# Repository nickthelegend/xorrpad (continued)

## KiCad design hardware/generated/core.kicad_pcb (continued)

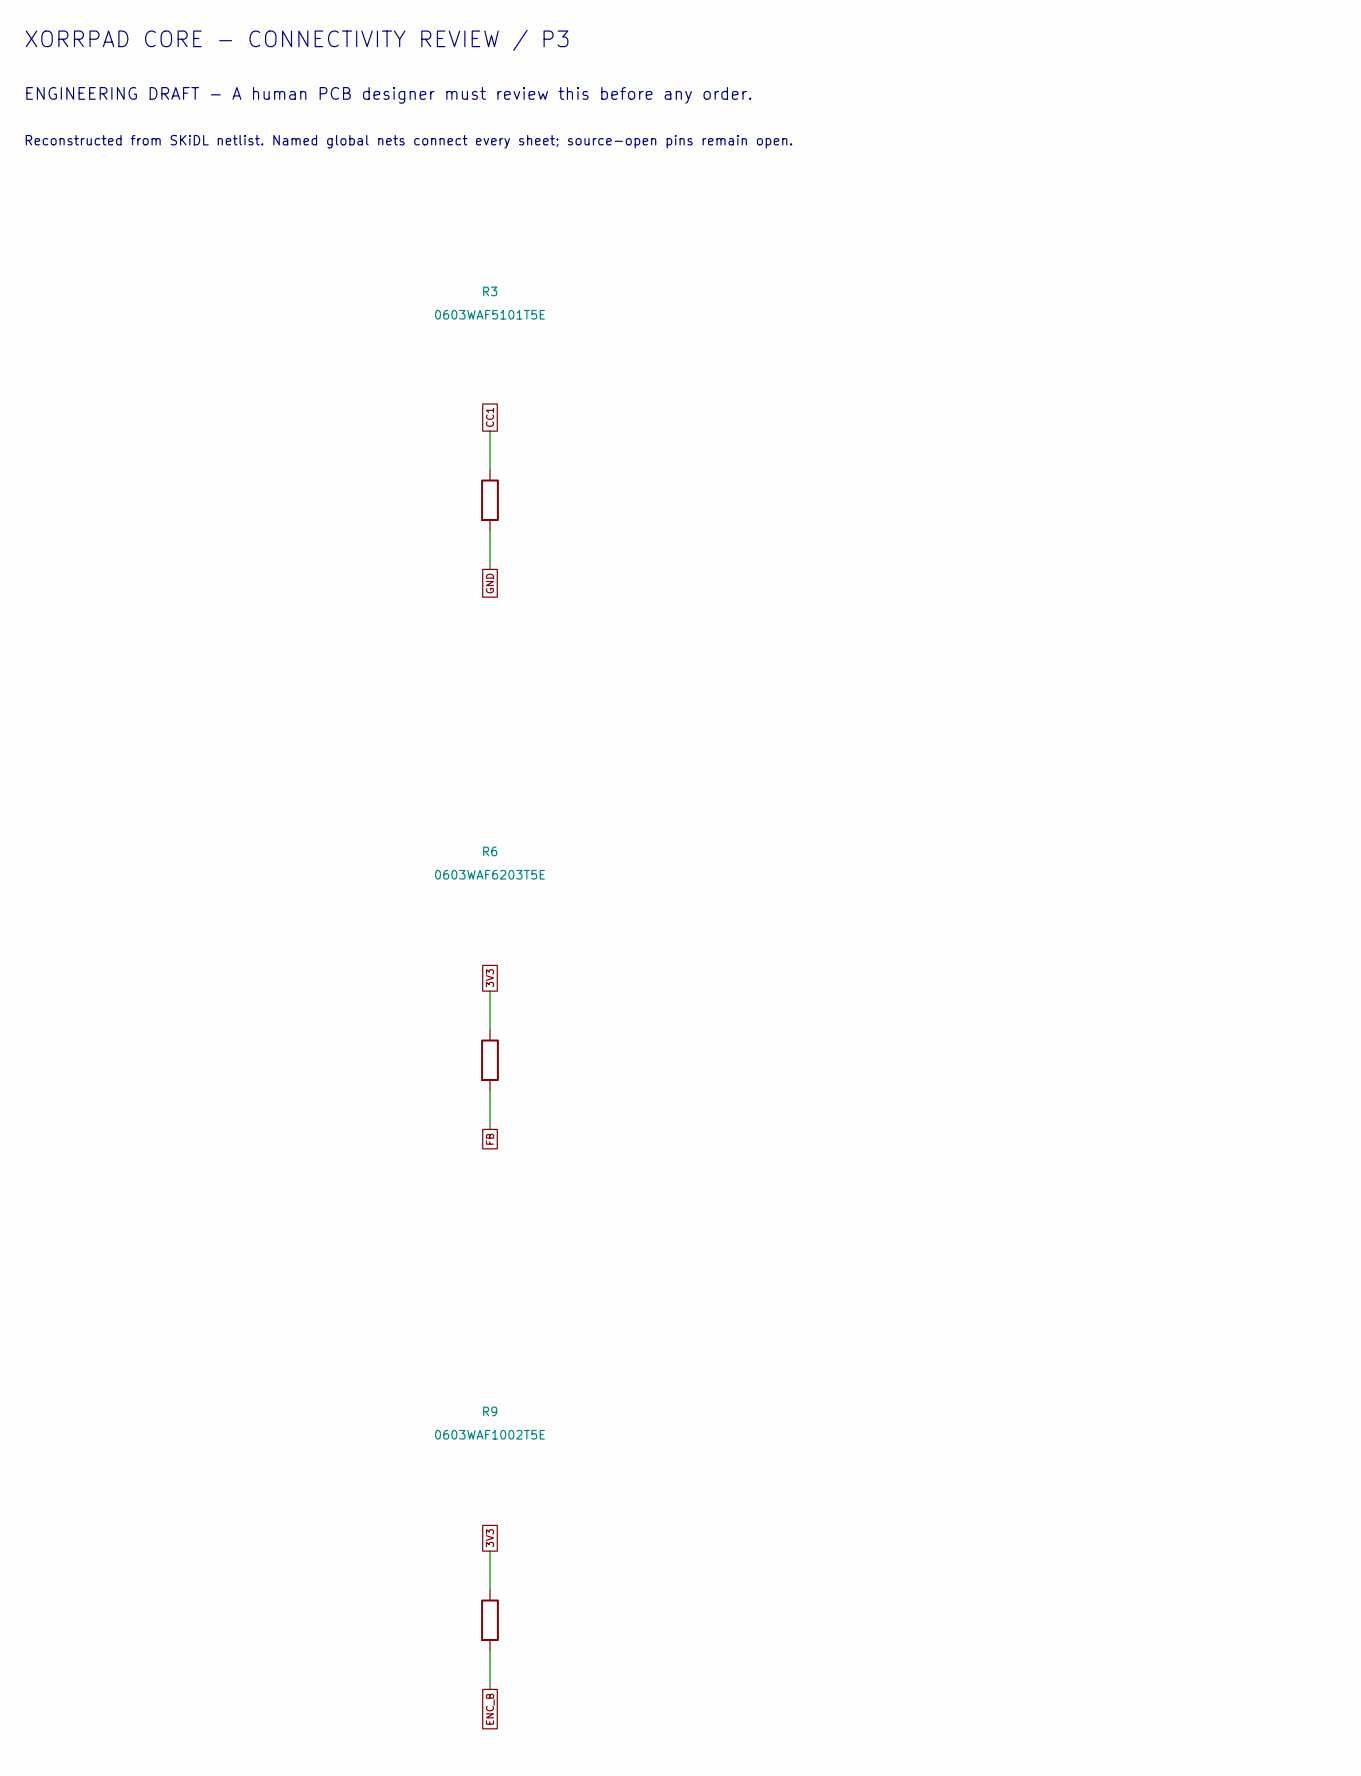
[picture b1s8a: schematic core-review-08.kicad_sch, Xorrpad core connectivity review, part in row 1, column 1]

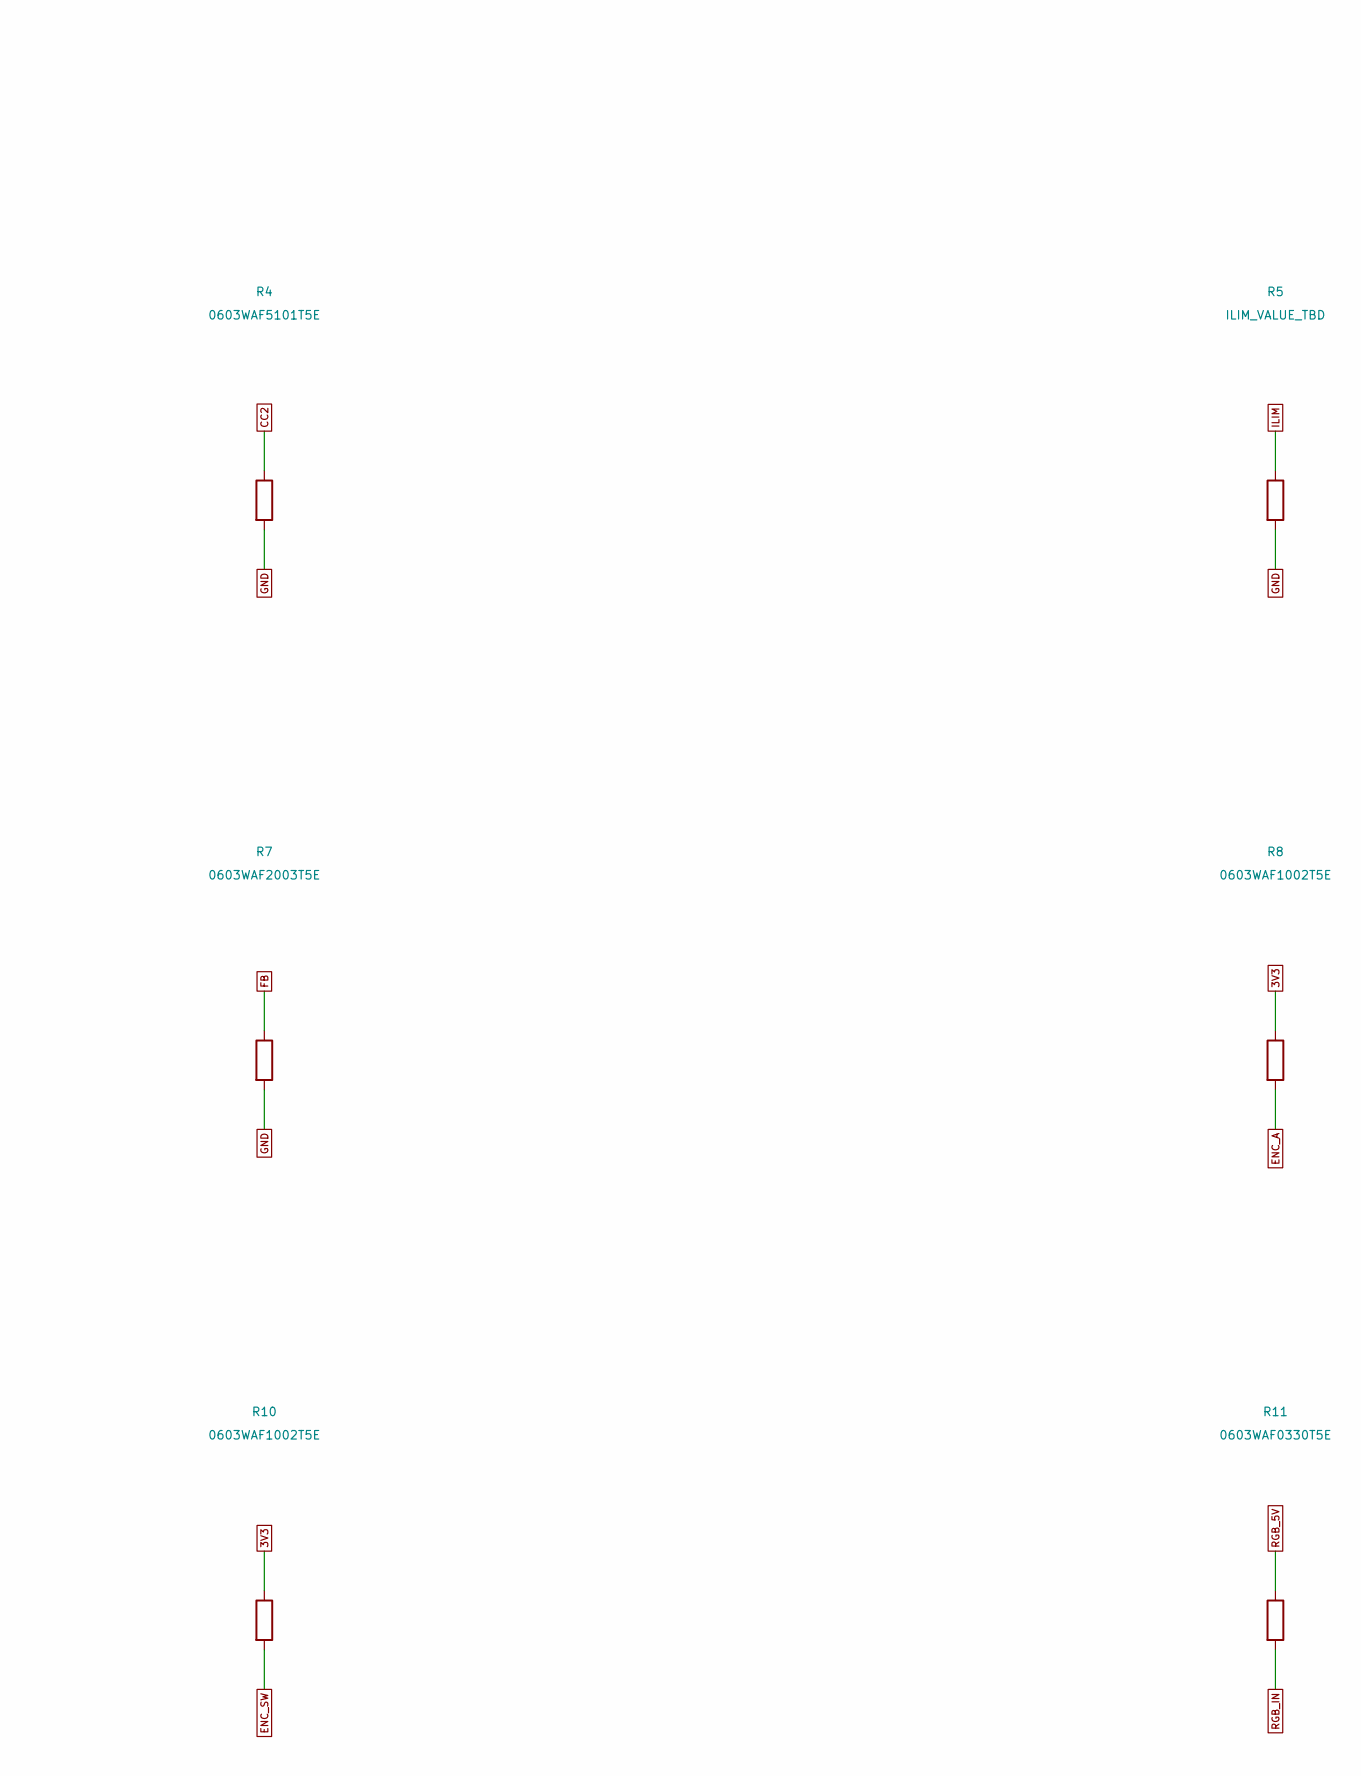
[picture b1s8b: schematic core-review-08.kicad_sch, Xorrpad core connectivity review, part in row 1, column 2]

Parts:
R3, R4: 0603WAF5101T5E; R_0603_1608Metric
R5: ILIM_VALUE_TBD; R_0603_1608Metric
R6: 0603WAF6203T5E; R_0603_1608Metric
R7: 0603WAF2003T5E; R_0603_1608Metric
R8, R9, R10: 0603WAF1002T5E; R_0603_1608Metric
R11: 0603WAF0330T5E; R_0603_1608Metric

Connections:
3V3: R6.1, R8.1, R9.1, R10.1; also elsewhere on the board
CC1: R3.1; also elsewhere on the board
CC2: R4.1; also elsewhere on the board
ENC_A: R8.2; also elsewhere on the board
ENC_B: R9.2; also elsewhere on the board
ENC_SW: R10.2; also elsewhere on the board
FB: R6.2, R7.1; also elsewhere on the board
GND: R3.2, R4.2, R5.2, R7.2; also elsewhere on the board
ILIM: R5.1; also elsewhere on the board
RGB_5V: R11.1; also elsewhere on the board
RGB_IN: R11.2; also elsewhere on the board

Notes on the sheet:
XORRPAD CORE - CONNECTIVITY REVIEW / P3
ENGINEERING DRAFT - A human PCB designer must review this before any order.
Reconstructed from SKiDL netlist. Named global nets connect every sheet; source-open pins remain open.

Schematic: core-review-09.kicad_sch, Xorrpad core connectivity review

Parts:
SW1, SW2, SW3, SW4, SW5, SW6, SW7, SW8, SW9: CPG151101S11; Kailh_CPG151101S11

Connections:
COL0: SW3.1, SW6.1; also elsewhere on the board
COL1: SW2.1, SW5.1; also elsewhere on the board
COL2: SW1.1, SW4.1, SW8.1, SW9.1; also elsewhere on the board
COL3: SW7.1; also elsewhere on the board
KEY1: SW1.2; also elsewhere on the board
KEY2: SW2.2; also elsewhere on the board
KEY3: SW3.2; also elsewhere on the board
KEY4: SW4.2; also elsewhere on the board
KEY5: SW5.2; also elsewhere on the board
KEY6: SW6.2; also elsewhere on the board
KEY7: SW7.2; also elsewhere on the board
KEY8: SW8.2; also elsewhere on the board
KEY9: SW9.2; also elsewhere on the board

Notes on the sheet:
XORRPAD CORE - CONNECTIVITY REVIEW / P3
ENGINEERING DRAFT - A human PCB designer must review this before any order.
Reconstructed from SKiDL netlist. Named global nets connect every sheet; source-open pins remain open.

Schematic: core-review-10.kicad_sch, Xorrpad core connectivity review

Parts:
SW10, SW11, SW12, SW13, SW14: CPG151101S11; Kailh_CPG151101S11
SW15, SW16: TS-1088-AR02016; SW_SPST_TL3342
U2: USBLC6-2SC6; SOT-666
U3: TPS62160DSGR; Texas_DSG0008A_WSON-8-1EP_2x2mm_P0.5mm_EP0.9x1.6mm_ThermalV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

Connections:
3V3: U3.6 (VOS); also elsewhere on the board
5V_LIMITED: U3.2 (VIN), U3.3 (EN); also elsewhere on the board
BOOT: SW15.1; also elsewhere on the board
BUCK_SW: U3.7 (SW); also elsewhere on the board
COL0: SW11.1, SW14.1; also elsewhere on the board
COL1: SW10.1, SW13.1; also elsewhere on the board
COL3: SW12.1; also elsewhere on the board
EN: SW16.1; also elsewhere on the board
FB: U3.5 (FB); also elsewhere on the board
GND: SW15.2, SW16.2, U2.2 (GND), U3.1 (PGND), U3.4 (AGND), U3.9 (PAD); also elsewhere on the board
KEY10: SW10.2; also elsewhere on the board
KEY11: SW11.2; also elsewhere on the board
KEY12: SW12.2; also elsewhere on the board
KEY13: SW13.2; also elsewhere on the board
KEY14: SW14.2; also elsewhere on the board
USB_DN: U2.3 (I/O2), U2.4 (I/O2); also elsewhere on the board
USB_DP: U2.1 (I/O1), U2.6 (I/O1); also elsewhere on the board
VBUS: U2.5 (VBUS); also elsewhere on the board

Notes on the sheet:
XORRPAD CORE - CONNECTIVITY REVIEW / P3
ENGINEERING DRAFT - A human PCB designer must review this before any order.
Reconstructed from SKiDL netlist. Named global nets connect every sheet; source-open pins remain open.

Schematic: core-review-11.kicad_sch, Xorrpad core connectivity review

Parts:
U4: SN74AHCT1G125DBVR; SOT-23-5
U8: TPS2553DBVR; SOT-23-6

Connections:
5V_LIMITED: U4.5 (VCC), U8.6 (OUT); also elsewhere on the board
GND: U4.1, U4.3 (GND), U8.2 (GND); also elsewhere on the board
ILIM: U8.5 (ILIM); also elsewhere on the board
RGB_3V3: U4.2; also elsewhere on the board
RGB_5V: U4.4; also elsewhere on the board
USB_FAULT: U8.4 (FAULT_N)
VBUS: U8.1 (IN), U8.3 (EN); also elsewhere on the board

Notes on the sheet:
XORRPAD CORE - CONNECTIVITY REVIEW / P3
ENGINEERING DRAFT - A human PCB designer must review this before any order.
Reconstructed from SKiDL netlist. Named global nets connect every sheet; source-open pins remain open.

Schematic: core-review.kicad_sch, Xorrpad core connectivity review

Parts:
U1: ESP32-S3-WROOM-1-N16R8; ESP32-S3-WROOM-1

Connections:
3V3: U1.2 (3V3); also elsewhere on the board
BOOT: U1.27 (IO0); also elsewhere on the board
COL0: U1.11 (IO18); also elsewhere on the board
COL1: U1.10 (IO17); also elsewhere on the board
COL2: U1.12 (IO8); also elsewhere on the board
COL3: U1.22 (IO14); also elsewhere on the board
EN: U1.3 (EN); also elsewhere on the board
ENC_A: U1.23 (IO21); also elsewhere on the board
ENC_B: U1.24 (IO47); also elsewhere on the board
ENC_SW: U1.31 (IO38); also elsewhere on the board
GND: U1.1 (GND), U1.40 (GND), U1.41 (GND); also elsewhere on the board
RGB_3V3: U1.25 (IO48); also elsewhere on the board
ROW0: U1.18 (IO10); also elsewhere on the board
ROW1: U1.19 (IO11); also elsewhere on the board
ROW2: U1.20 (IO12); also elsewhere on the board
ROW3: U1.21 (IO13); also elsewhere on the board
USB_DN: U1.13 (USB_D-); also elsewhere on the board
USB_DP: U1.14 (USB_D+); also elsewhere on the board

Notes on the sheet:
XORRPAD CORE - CONNECTIVITY REVIEW / P3
ENGINEERING DRAFT - A human PCB designer must review this before any order.
Reconstructed from SKiDL netlist. Named global nets connect every sheet; source-open pins remain open.
Review holds: ILIM_VALUE_TBD; USB/RF/power; sourcing; enclosure supports.
Pro J3 and U8 use the source passive terminal models; no functional certification.

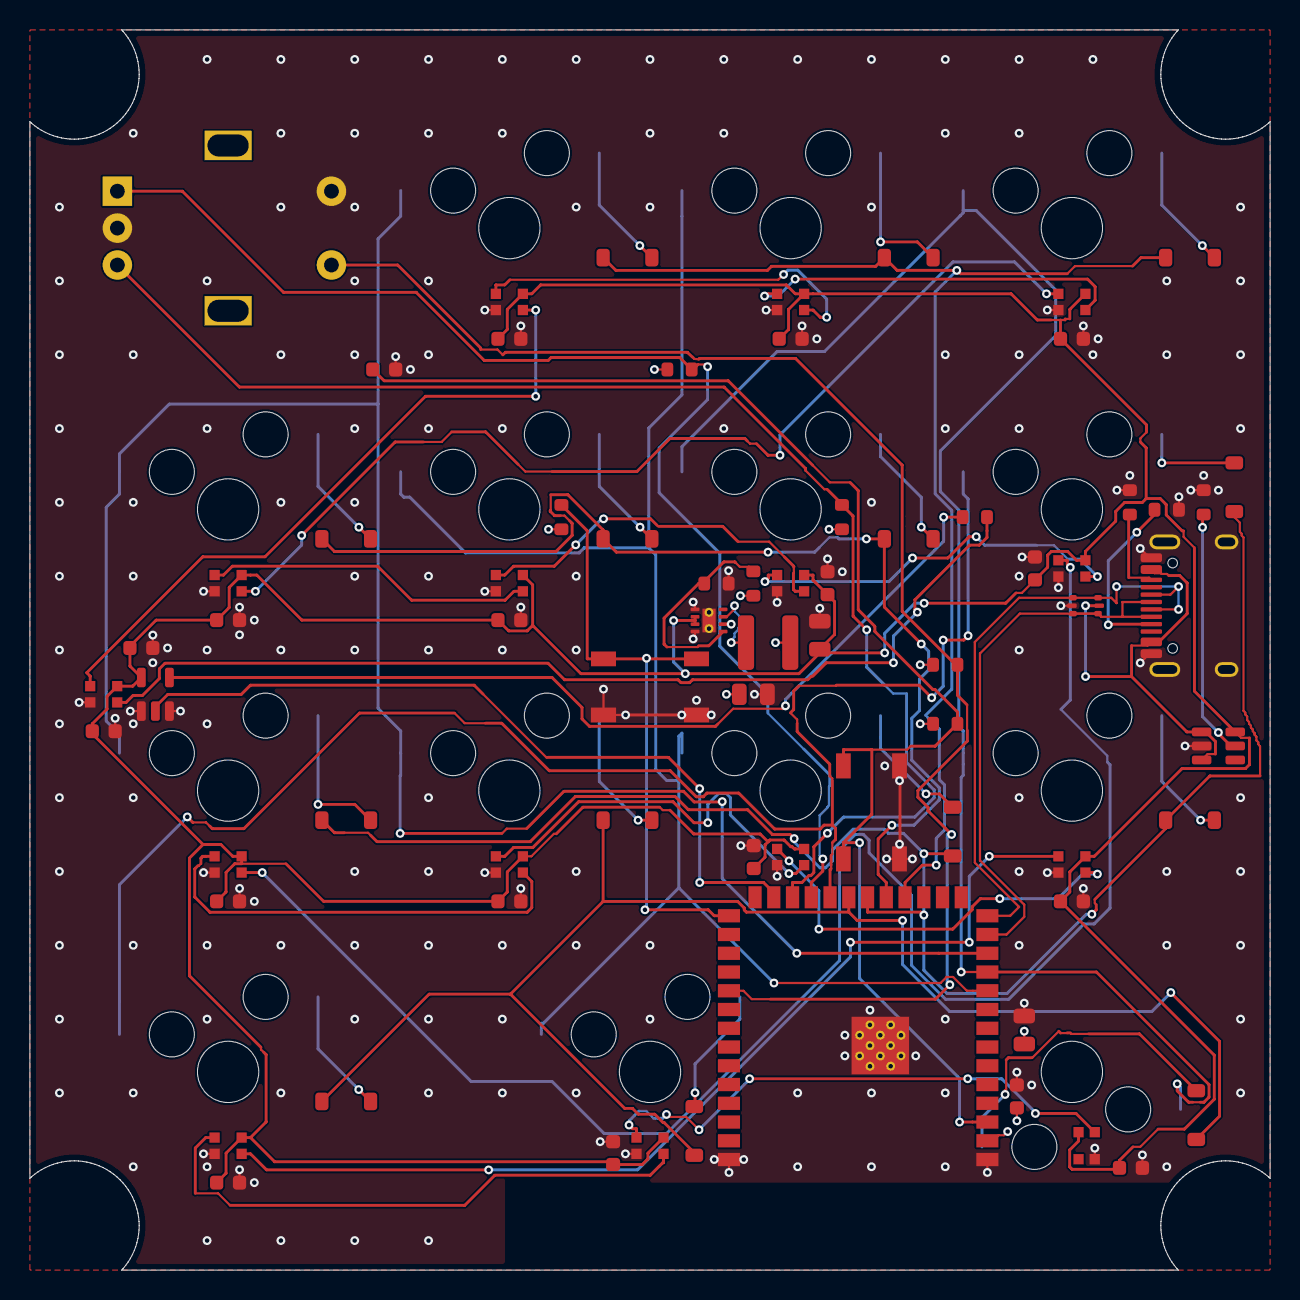
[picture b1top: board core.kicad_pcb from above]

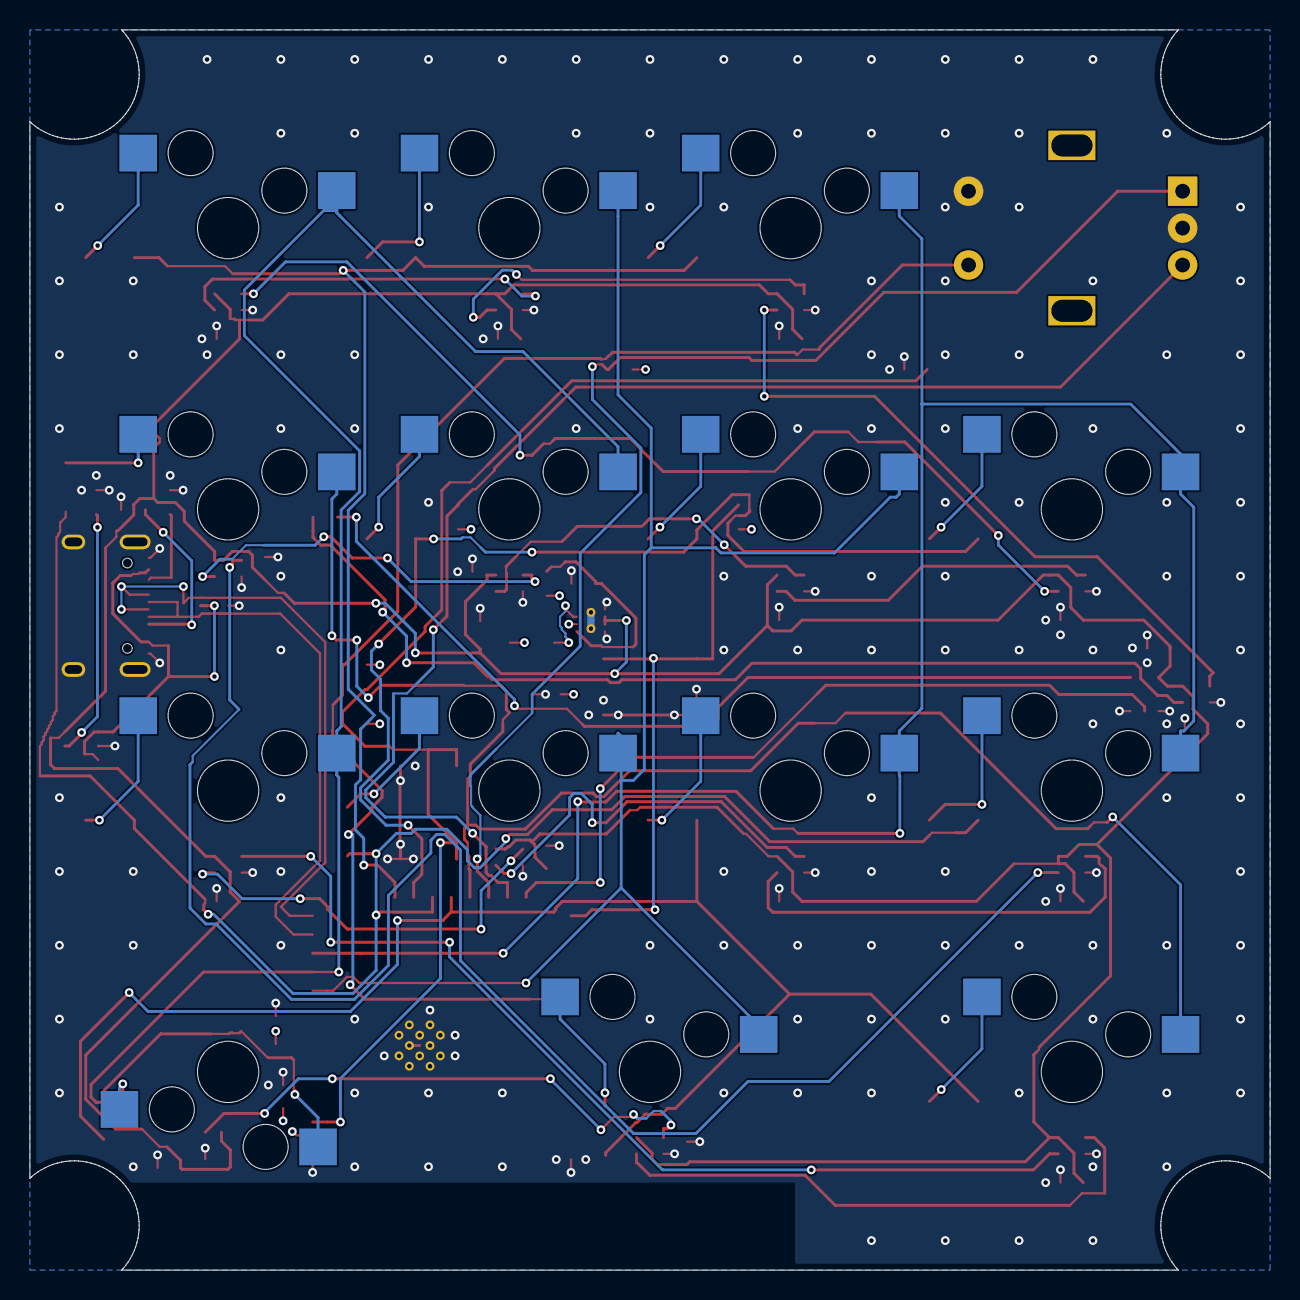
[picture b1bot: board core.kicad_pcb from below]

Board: 4 copper layers, 84.0 x 84.0 mm, 85 parts (14 on the bottom side), 55 nets.

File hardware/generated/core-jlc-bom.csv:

Comment,Designator,Footprint,LCSC Part #
0603WAF0330T5E,R11,Resistor_SMD:R_0603_1608Metric,
0603WAF1002T5E,"R1,R2,R8,R9,R10",Resistor_SMD:R_0603_1608Metric,C25804
0603WAF2003T5E,R7,Resistor_SMD:R_0603_1608Metric,
0603WAF5101T5E,"R3,R4",Resistor_SMD:R_0603_1608Metric,C23186
0603WAF6203T5E,R6,Resistor_SMD:R_0603_1608Metric,
1N4148W,"D1,D2,D3,D4,D5,D6,D7,D8,D9,D10,D11,D12,D13,D14",Diode_SMD:D_SOD-123,C81598
CC0603KRX7R9BB104,"C1,C2,C6,C20,C21,C22,C23,C24,C25,C26,C27,C28,C29,C30,C31,C32,C33,C34",Capacitor_SMD:C_0603_1608Metric,C14663
CPG151101S11,"SW1,SW2,SW3,SW4,SW5,SW6,SW7,SW8,SW9,SW10,SW11,SW12,SW13,SW14",Xorrpad:Kailh_CPG151101S11,C2803348
EC11E15244G1,ENC1,Rotary_Encoder:RotaryEncoder_Alps_EC11E-Switch_Vertical_H20mm,C370970
ESP32-S3-WROOM-1-N16R8,U1,RF_Module:ESP32-S3-WROOM-1,C2913202
GRM21BR61A226ME44L,"C3,C4,C5",Capacitor_SMD:C_0805_2012Metric,C441864
ILIM_VALUE_TBD,R5,Resistor_SMD:R_0603_1608Metric,
SN74AHCT1G125DBVR,U4,Package_TO_SOT_SMD:SOT-23-5,C7484
SWPA4026S2R2MT,L1,Inductor_SMD:L_Sunlord_SWPA4026S,
TPS2553DBVR,U8,Package_TO_SOT_SMD:SOT-23-6,
TPS62160DSGR,U3,Package_SON:Texas_DSG0008A_WSON-8-1EP_2x2mm_P0.5mm_EP0.9x1.6mm_ThermalVias,C324077
TS-1088-AR02016,"SW15,SW16",Button_Switch_SMD:SW_SPST_TL3342,
TYPE-C-31-M-12,J1,Connector_USB:USB_C_Receptacle_HRO_TYPE-C-31-M-12,C165948
USBLC6-2SC6,U2,Package_TO_SOT_SMD:SOT-666,C7519
WS2812B-2020-V6,"LED1,LED2,LED3,LED4,LED5,LED6,LED7,LED8,LED9,LED10,LED11,LED12,LED13,LED14,LED15",LED_SMD:LED_WS2812B-2020_PLCC4_2.0x2.0mm,C52917434
